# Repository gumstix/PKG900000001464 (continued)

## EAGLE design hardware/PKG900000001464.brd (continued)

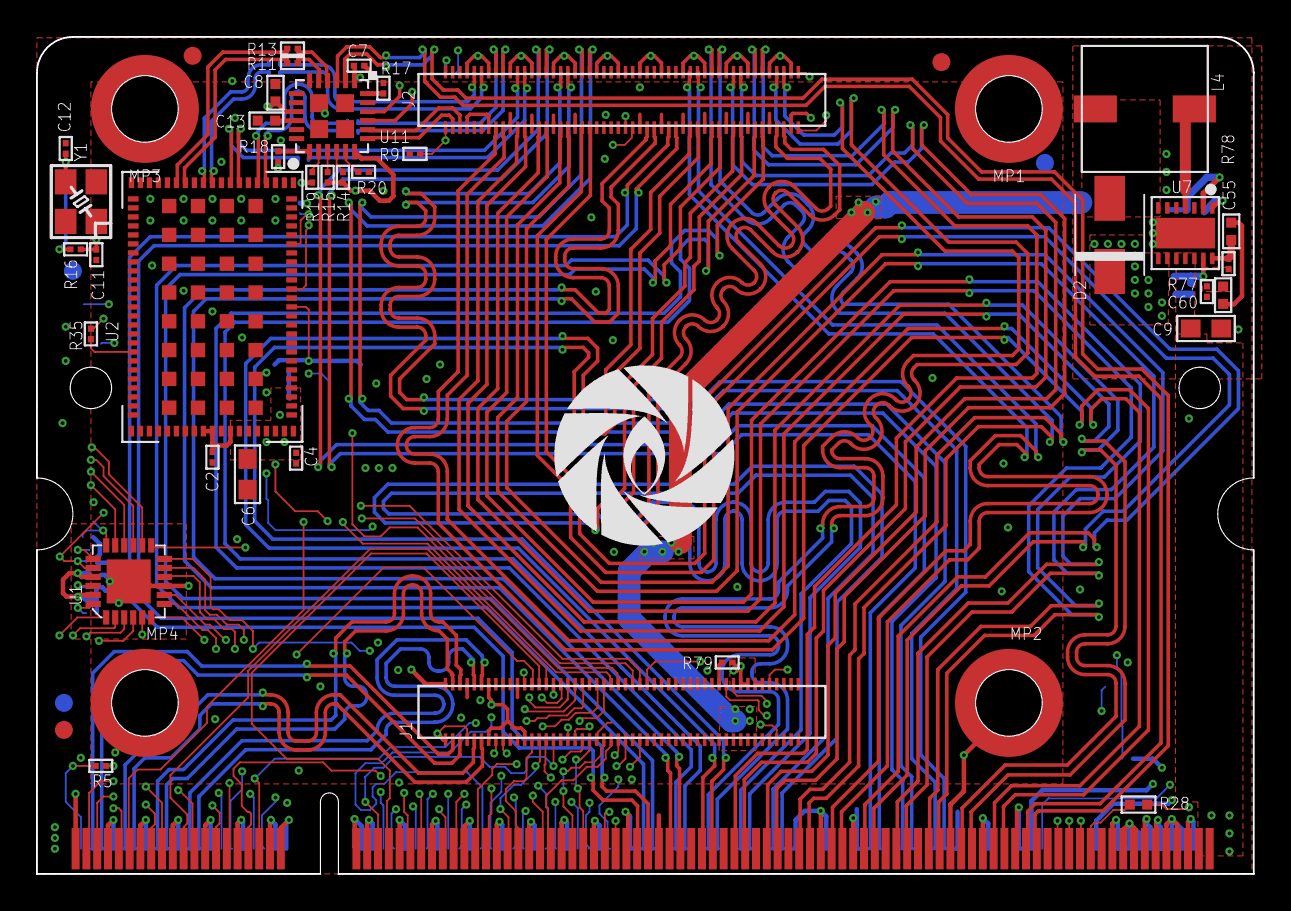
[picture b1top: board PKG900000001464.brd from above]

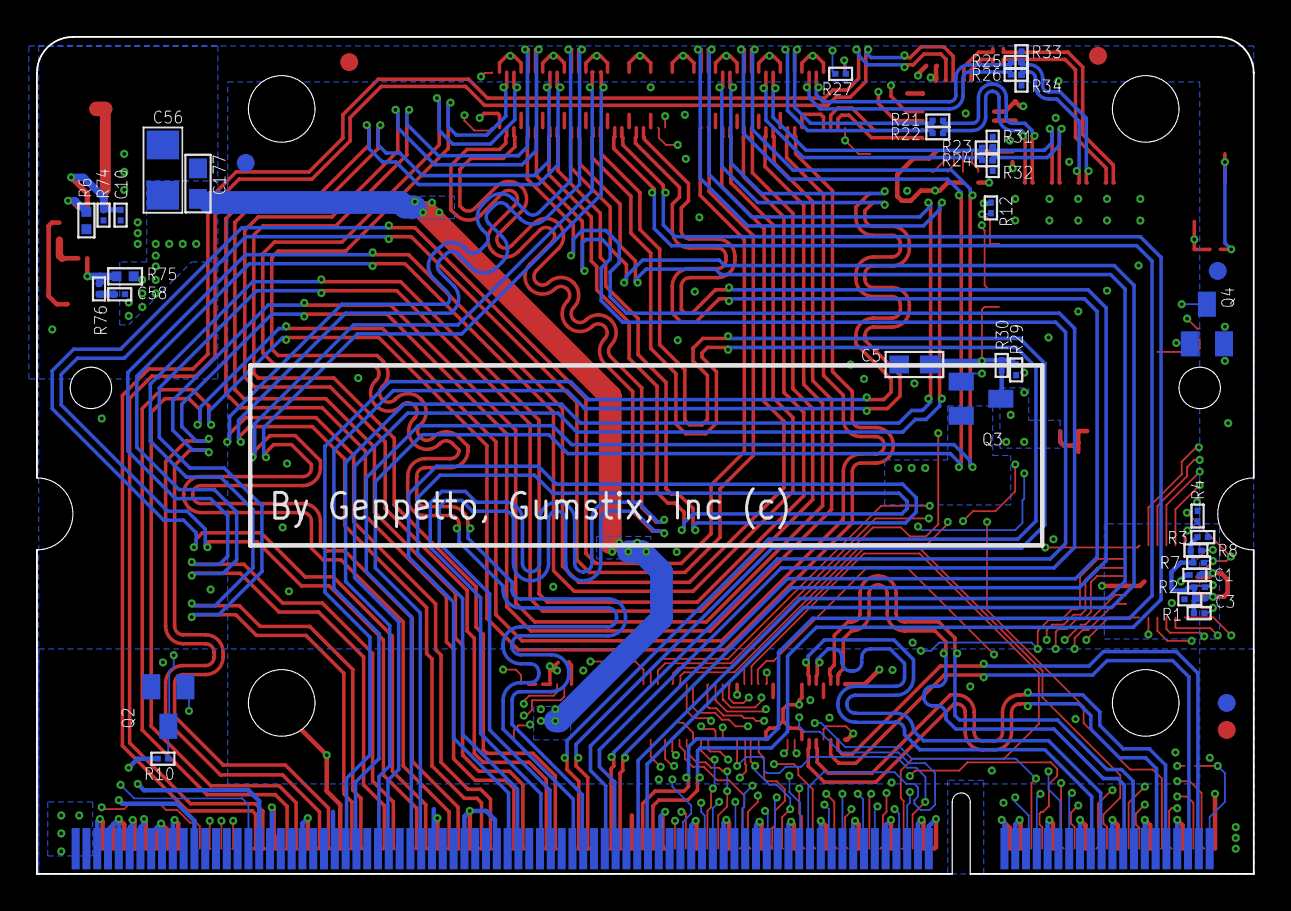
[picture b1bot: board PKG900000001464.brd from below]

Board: 6 copper layers, 67.6 x 46.5 mm, 84 parts (39 on the bottom side), 164 nets.

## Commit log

2020-10-13 Add README content, spec sheet, autodoc and folders
2020-10-15 Added hardware documents for revision 3.
2020-10-15 add links to hardware
